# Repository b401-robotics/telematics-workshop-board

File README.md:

<!-- center -->
<h1 align="center">Telematics Workshop Board</h1>

<p align="center">
	</a>
	</a>
	</a>
</p>

This repository contains the documentation for the Workshop Telematics Board. The board is based on the ESP8266 microcontroller and has several features that can be used for various projects.

<!-- beritahu versi lawas -->
> For the previous version of the board, refer to the [v1 board.](https://github.com/b401-robotics/esp8266-minsys)

## 🌟 Features

The following are the features available on this board.

- ESP-12F (ESP8266)
- 8 GPIO Pins
- Programmable RGB LED
- Overcurrent Protection
- USB Type-C Connector (_Power Delivery Support_) 

## 👀 Preview

Here is a preview of the board that will be used in the workshop.

## 📚 Resources

For more information about the board, you can check the following resources.

- [Hardware](hardware/)
- [Firmware](firmware/)

## 🔮 Project Showcase

Discover projects that use this board in various applications and contexts.

- [🌌 __COMING SOON__]() by [farisrfp](https://farisrfp.me)

## 📝 License

Distributed under the MIT License. See `LICENSE` for more information.

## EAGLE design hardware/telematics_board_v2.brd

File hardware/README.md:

# **Hardware**

This folder contains the hardware design for the Telematics Workshop Board.

## 🚀 Getting Started

### Prerequisites

- [Eagle](https://www.autodesk.com/products/eagle/overview) 
- [Fusion 360](https://www.autodesk.com/products/fusion-360/overview)

## 🕸 Schematic

This is the schematic diagram for the Board will be used in the workshop.

## 💲 Bill of Material

|   Designator   | Quantity | Package | Value  |      Description      |
|:--------------:|:--------:|:-------:|:------:|:---------------------:|
|    ESP-12F     |    1     |    -    |   -    |    ESP8266 Module     |
|       U1       |    1     | SOP-16  | CH340C |    IC USB to UART     |
|       U2       |    1     | SOT-223 |  3V3   | Voltage Regulator 3V3 |
|       D1       |    1     |  0805   |  Red   |          LED          |
|      NEO       |    1     |  5050   |  RGB   |        WS2812B        |
|       F1       |    1     |  1206   | 750mA  |    Resettable Fuse    |
|       J1       |    1     |    -    |  16P   |      USB Type-C       |
|   BOOT, RST    |    2     |    -    |   -    |      Push Button      |
| R1, R2, R3, R4 |    4     |  0805   |  10K   |       Resistor        |
|     R5, R6     |    2     |  0805   |  5.1K  |       Resistor        |
|       R7       |    1     |  0805   |   1K   |       Resistor        |
|       C1       |    1     |  2412   |  100u  |   Capacitor (Polar)   |
|     C2, C3     |    2     |  0805   |  10u   | Capacitor (Nonpolar)  |
|       C4       |    1     |  0805   |   1u   | Capacitor (Nonpolar)  |
|       C5       |    1     |  0805   |  10n   | Capacitor (Nonpolar)  |
|     Q1, Q2     |    2     | SOT-23  | BSS138 |   N-Channel MOSFET    |

## 👨‍🔧 PCB Assembly

Refer to the image below for detailed placement and routing.

> Click the image to view the full resolution.

### SMD Polarity

SMD LEDs have 2 pins, namely the anode and cathode pins. Refer to the image below to determine which pin is the anode and cathode.

The Tantalum Capacitor is one of the polar capacitors. Refer to the image below to determine which pin is the anode(+).

## 📚 Resources

### Telematics Workshop Board

Access the design files for the Telematics Workshop Board directly from this repository:

- [Schematic](./telematics_board_v2.sch)
- [Board Design](./telematics_board_v2.brd)
- [3D Model](./telematics_board_v2.step)
- [Eagle/Fusion 360 Library](libraries/)

### Enclosure

Access the 3D printable enclosure files from this repository, with contributions from the following individuals:

- [B401 Robotics]()

<!-- ## SMD Polarity

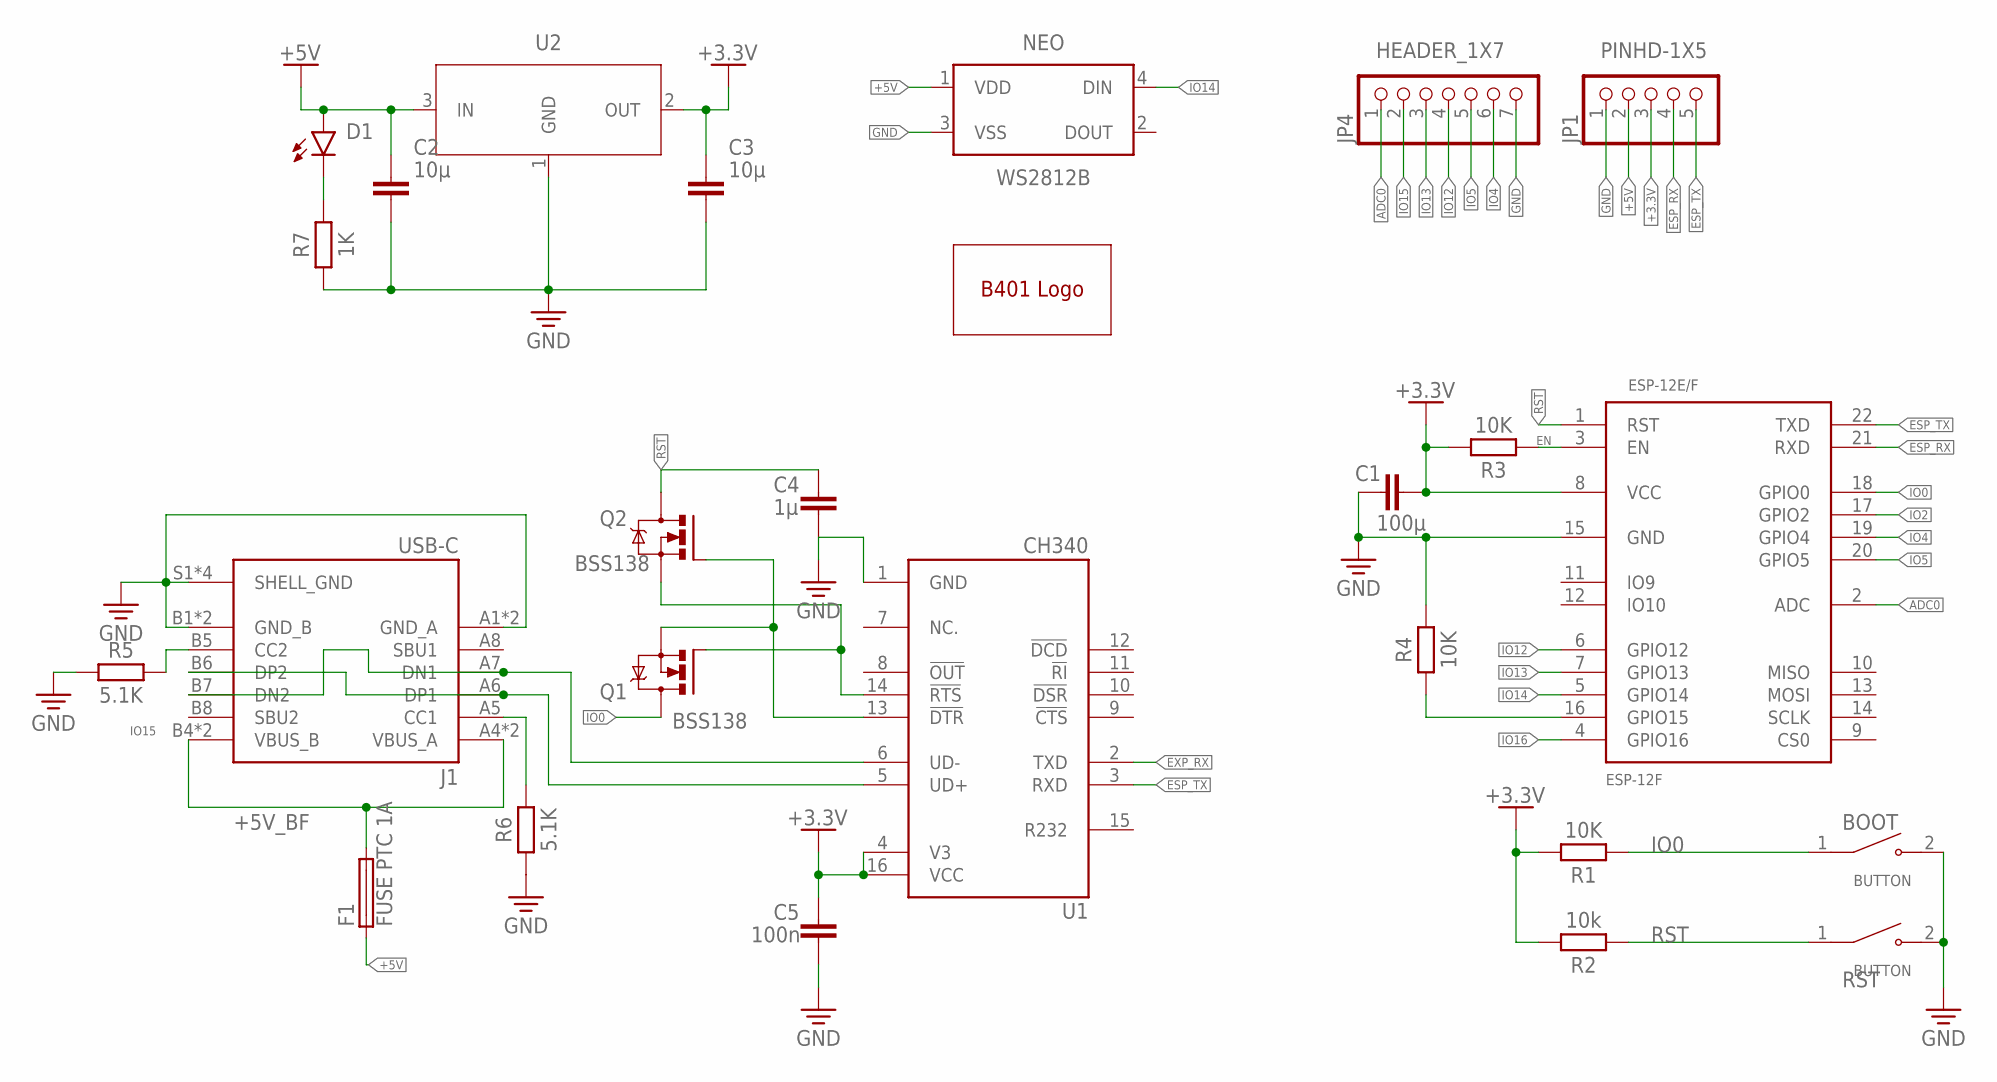
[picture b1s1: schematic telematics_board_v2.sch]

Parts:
BOOT: BUTTON; SWITCH-2P
C1: 100µ; CAPM6032X280
C2, C3: 10µ; CAPC2012X110
C4: 1µ; CAPC2012X110
C5: 100n; CAPC2012X110
D1: LED_RED; LEDC2012X110N_FLAT-R
ESP-12E/F: ESP-12F
F1: FUSE PTC 1A; FUSC3215X82N
J1: USB-C; USB-C-16P
JP1: PINHD-1X5; 1X05
JP4: HEADER_1X7; 1X07
NEO: WS2812B
Q1, Q2: BSS138; SOT23
R1, R3, R4: 10K; RESC2012X65
R2: 10k; RESC2012X65
R5, R6: 5.1K; RESC2012X65
R7: 1K; RESC2012X65
RST: BUTTON; SWITCH-2P
U1: CH340; SOIC127P600X180-16N
U2: NCP1117ST33T3G; SOT230P700X170-4
U$1: LOGO_B401LARGE; B401_LARGE

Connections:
+3.3V: C1.2, C3.1, C5.1, ESP-12E/F.8 (VCC), JP1.3, R1.2, R2.2, R3.2, U1.4 (V3), U1.16 (VCC), U2.2 (OUT)
+5V: C2.1, D1.A, F1.1, JP1.2, NEO.1 (VDD), U2.3 (IN)
+5V_BF: F1.2, J1.A4 (VBUS_A), J1.A9 (VBUS_A), J1.B4 (VBUS_B), J1.B9 (VBUS_B)
ADC0: ESP-12E/F.2 (ADC), JP4.1
EN: ESP-12E/F.3 (EN), R3.1
ESP_RX: ESP-12E/F.21 (RXD), JP1.4
ESP_TX: ESP-12E/F.22 (TXD), JP1.5, U1.3 (RXD)
EXP_RX: U1.2 (TXD)
GND: BOOT.2, C1.1, C2.2, C3.2, C4.2, C5.2, ESP-12E/F.15 (GND), J1.A1 (GND_A), J1.A12 (GND_A), J1.B1 (GND_B), J1.B12 (GND_B), J1.S1 (SHELL_GND), J1.S2 (SHELL_GND), J1.S3 (SHELL_GND), J1.S4 (SHELL_GND), JP1.1, JP4.7, NEO.3 (VSS), R4.2, R5.1, R6.1, R7.1, RST.2, U1.1 (GND), U2.1 (GND)
IO0: BOOT.1, ESP-12E/F.18 (GPIO0), Q1.3 (D), R1.1
IO2: ESP-12E/F.17 (GPIO2)
IO4: ESP-12E/F.19 (GPIO4), JP4.6
IO5: ESP-12E/F.20 (GPIO5), JP4.5
IO12: ESP-12E/F.6 (GPIO12), JP4.4
IO13: ESP-12E/F.7 (GPIO13), JP4.3
IO14: ESP-12E/F.5 (GPIO14), NEO.4 (DIN)
IO15: ESP-12E/F.16 (GPIO15), JP4.2, R4.1
IO16: ESP-12E/F.4 (GPIO16)
unnamed: J1.A6 (DP1), J1.B6 (DP2), U1.5 (UD+)
unnamed: J1.A7 (DN1), J1.B7 (DN2), U1.6 (UD-)
unnamed: Q1.2 (S), Q2.1 (G), U1.13 (!DTR)
unnamed: J1.B5 (CC2), R5.2
unnamed: J1.A5 (CC1), R6.2
unnamed: Q1.1 (G), Q2.2 (S), U1.14 (!RTS)
unnamed: D1.C, R7.2
RST: C4.1, ESP-12E/F.1 (RST), Q2.3 (D), R2.1, RST.1

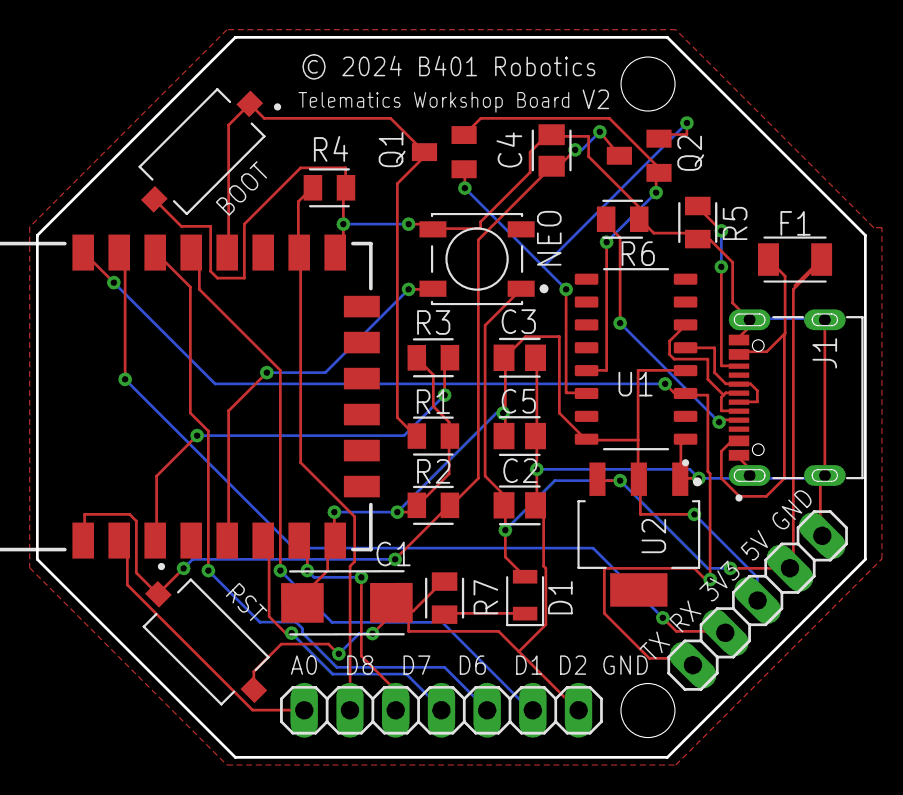
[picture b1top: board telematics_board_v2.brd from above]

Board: 2 copper layers, 46.0 x 40.0 mm, 26 parts (1 on the bottom side), 23 nets.

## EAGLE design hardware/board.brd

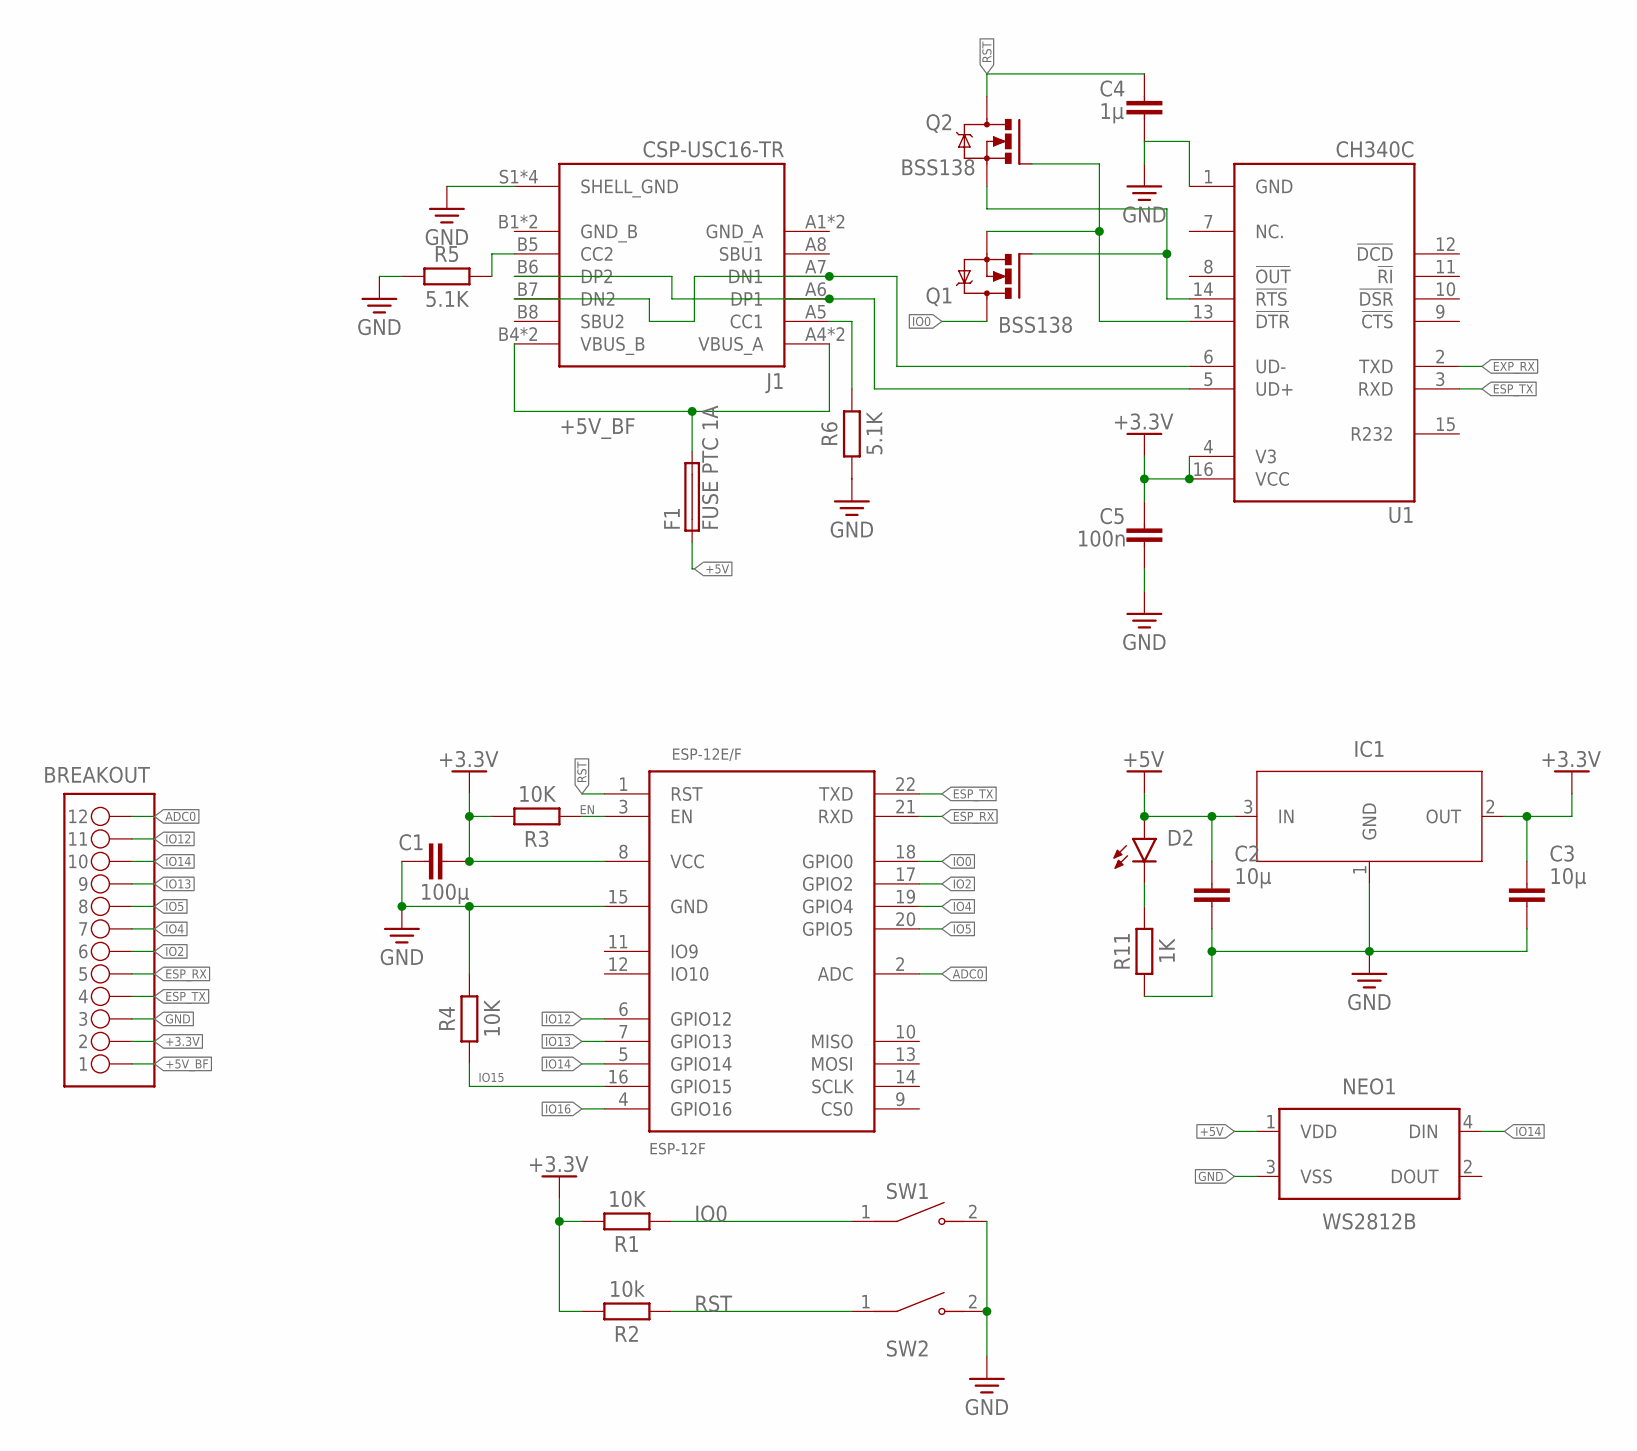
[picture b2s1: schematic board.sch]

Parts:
BREAKOUT: PINHD-1X12-BACKUP_1X12M; 1X12
C1: 100µ; CAPM6032X280
C2, C3: 10µ; CAPC2012X110
C4: 1µ; CAPC2012X110
C5: 100n; CAPC2012X110
D2: LED_RED; LEDC2012X110N_FLAT-R
ESP-12E/F: ESP-12F
F1: FUSE PTC 1A; FUSC3215X82N
IC1: NCP1117ST33T3G; SOT230P700X170-4
J1: CSP-USC16-TR; VALCON_CSP-USC16-TR
NEO1: WS2812B
Q1, Q2: BSS138; SOT23
R1, R3, R4: 10K; RESC2012X65
R2: 10k; RESC2012X65
R5, R6: 5.1K; RESC2012X65
R11: 1K; RESC2012X65
SW1, SW2: SWITCH-2P
U1: CH340C; SOIC127P600X180-16N

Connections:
+3.3V: BREAKOUT.2, C1.2, C3.1, C5.1, ESP-12E/F.8 (VCC), IC1.2 (OUT), R1.2, R2.2, R3.2, U1.4 (V3), U1.16 (VCC)
+5V: C2.1, D2.A, F1.1, IC1.3 (IN), NEO1.1 (VDD)
+5V_BF: BREAKOUT.1, F1.2, J1.A4 (VBUS_A), J1.A9 (VBUS_A), J1.B4 (VBUS_B), J1.B9 (VBUS_B)
ADC0: BREAKOUT.12, ESP-12E/F.2 (ADC)
EN: ESP-12E/F.3 (EN), R3.1
ESP_RX: BREAKOUT.5, ESP-12E/F.21 (RXD)
ESP_TX: BREAKOUT.4, ESP-12E/F.22 (TXD), U1.3 (RXD)
EXP_RX: U1.2 (TXD)
GND: BREAKOUT.3, C1.1, C2.2, C3.2, C4.2, C5.2, ESP-12E/F.15 (GND), IC1.1 (GND), J1.S1 (SHELL_GND), J1.S2 (SHELL_GND), J1.S3 (SHELL_GND), J1.S4 (SHELL_GND), NEO1.3 (VSS), R4.2, R5.1, R6.1, R11.1, SW1.2, SW2.2, U1.1 (GND)
GND_A: J1.A1 (GND_A), J1.A12 (GND_A)
GND_B: J1.B1 (GND_B), J1.B12 (GND_B)
IO0: ESP-12E/F.18 (GPIO0), Q1.3 (D), R1.1, SW1.1
IO2: BREAKOUT.6, ESP-12E/F.17 (GPIO2)
IO4: BREAKOUT.7, ESP-12E/F.19 (GPIO4)
IO5: BREAKOUT.8, ESP-12E/F.20 (GPIO5)
IO12: BREAKOUT.11, ESP-12E/F.6 (GPIO12)
IO13: BREAKOUT.9, ESP-12E/F.7 (GPIO13)
IO14: BREAKOUT.10, ESP-12E/F.5 (GPIO14), NEO1.4 (DIN)
IO15: ESP-12E/F.16 (GPIO15), R4.1
IO16: ESP-12E/F.4 (GPIO16)
unnamed: J1.A6 (DP1), J1.B6 (DP2), U1.5 (UD+)
unnamed: J1.A7 (DN1), J1.B7 (DN2), U1.6 (UD-)
unnamed: Q1.2 (S), Q2.1 (G), U1.13 (!DTR)
unnamed: J1.B5 (CC2), R5.2
unnamed: J1.A5 (CC1), R6.2
unnamed: Q1.1 (G), Q2.2 (S), U1.14 (!RTS)
unnamed: D2.C, R11.2
RST: C4.1, ESP-12E/F.1 (RST), Q2.3 (D), R2.1, SW2.1

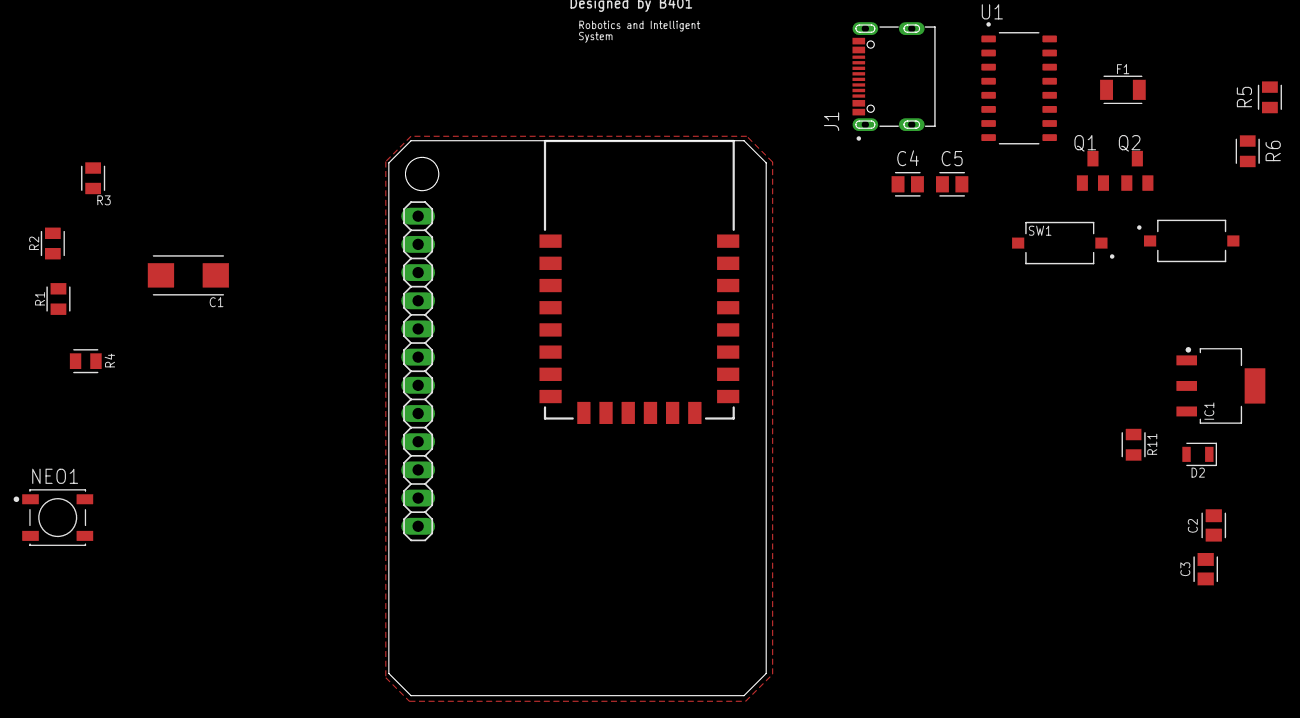
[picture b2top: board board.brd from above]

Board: 2 copper layers, 24 parts (0 on the bottom side), 26 nets.

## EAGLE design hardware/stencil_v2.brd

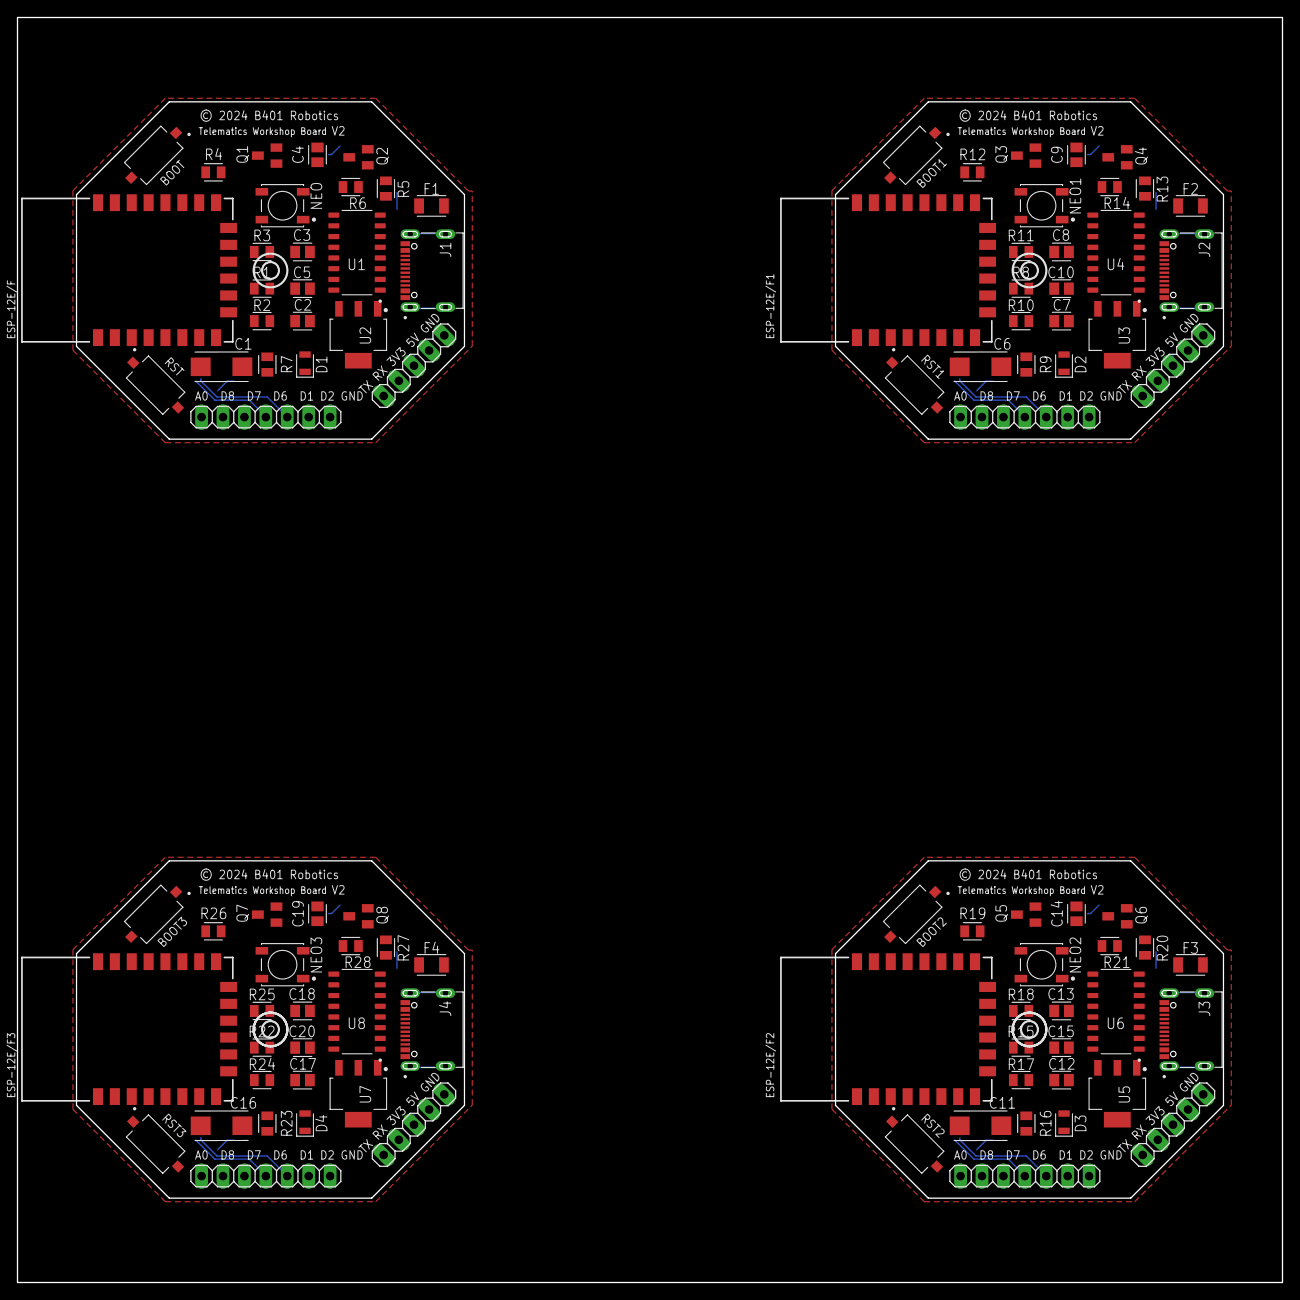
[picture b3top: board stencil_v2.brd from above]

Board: 2 copper layers, 150.0 x 150.0 mm, 100 parts (0 on the bottom side), 88 nets.

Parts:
BOOT, BOOT1, BOOT2, BOOT3: BUTTON; SWITCH-2P
C1, C6, C11, C16: 100µ; CAPM6032X280
C2, C3, C7, C8, C12, C13, C17, C18: 10µ; CAPC2012X110
C4, C9, C14, C19: 1µ; CAPC2012X110
C5, C10, C15, C20: 100n; CAPC2012X110
D1, D2, D3, D4: LED_RED; LEDC2012X110N_FLAT-R
ESP-12E/F, ESP-12E/F1, ESP-12E/F2, ESP-12E/F3: ESP-12F
F1, F2, F3, F4: FUSE PTC 1A; FUSC3215X82N
J1, J2, J3, J4: USB-C; USB-C-16P
JP1, JP3, JP6, JP8: PINHD-1X5; 1X05
JP2, JP4, JP5, JP7: HEADER_1X7; 1X07
NEO, NEO1, NEO2, NEO3: WS2812B
Q1, Q2, Q3, Q4, Q5, Q6, Q7, Q8: BSS138; SOT23
R1, R3, R4, R8, R11, R12, R15, R18, R19, R22, R25, R26: 10K; RESC2012X65
R2, R10, R17, R24: 10k; RESC2012X65
R5, R6, R13, R14, R20, R21, R27, R28: 5.1K; RESC2012X65
R7, R9, R16, R23: 1K; RESC2012X65
RST, RST1, RST2, RST3: BUTTON; SWITCH-2P
U1, U4, U6, U8: CH340; SOIC127P600X180-16N
U2, U3, U5, U7: NCP1117ST33T3G; SOT230P700X170-4

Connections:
+3.3V: C3.1, C5.1, U1.4, U1.16, U2.2
+3.3V1: C8.1, C10.1, U3.2, U4.4, U4.16
+3.3V2: C13.1, C15.1, U5.2, U6.4, U6.16
+3.3V3: C18.1, C20.1, U7.2, U8.4, U8.16
+5V: F1.1, JP1.2
+5V1: F2.1, JP3.2
+5V2: F3.1, JP6.2
+5V3: F4.1, JP8.2
+5V_BF: F1.2, J1.A4, J1.A9, J1.B4, J1.B9
+5V_BF1: F2.2, J2.A4, J2.A9, J2.B4, J2.B9
+5V_BF2: F3.2, J3.A4, J3.A9, J3.B4, J3.B9
+5V_BF3: F4.2, J4.A4, J4.A9, J4.B4, J4.B9
ADC0: ESP-12E/F.2, JP4.1
ADC1: ESP-12E/F1.2, JP2.1
ADC2: ESP-12E/F2.2, JP5.1
ADC3: ESP-12E/F3.2, JP7.1
ESP_TX: JP1.5, U1.3
ESP_TX1: JP3.5, U4.3
ESP_TX2: JP6.5, U6.3
ESP_TX3: JP8.5, U8.3
GND: C4.2, J1.A1, J1.A12, J1.B1, J1.B12, J1.S1, J1.S2, J1.S3, J1.S4, JP1.1, NEO.3, R5.1, R6.1
GND1: C9.2, J2.A1, J2.A12, J2.B1, J2.B12, J2.S1, J2.S2, J2.S3, J2.S4, JP3.1, NEO1.3, R13.1, R14.1
GND2: C14.2, J3.A1, J3.A12, J3.B1, J3.B12, J3.S1, J3.S2, J3.S3, J3.S4, JP6.1, NEO2.3, R20.1, R21.1
GND3: C19.2, J4.A1, J4.A12, J4.B1, J4.B12, J4.S1, J4.S2, J4.S3, J4.S4, JP8.1, NEO3.3, R27.1, R28.1
IO0: BOOT.1, ESP-12E/F.18, Q1.3, R1.1
IO1: BOOT1.1, ESP-12E/F1.18, Q3.3, R8.1
IO3: ESP-12E/F1.6, JP2.4
IO12: ESP-12E/F.6, JP4.4
IO15: ESP-12E/F.16, JP4.2, R4.1
IO17: ESP-12E/F1.16, JP2.2, R12.1
IO18: BOOT2.1, ESP-12E/F2.18, Q5.3, R15.1
IO19: ESP-12E/F2.6, JP5.4
IO26: ESP-12E/F2.16, JP5.2, R19.1
IO27: BOOT3.1, ESP-12E/F3.18, Q7.3, R22.1
IO28: ESP-12E/F3.6, JP7.4
IO35: ESP-12E/F3.16, JP7.2, R26.1
unnamed: J1.A6, J1.B6, U1.5
unnamed: J1.A7, J1.B7, U1.6
unnamed: Q1.2, Q2.1
unnamed: J1.B5, R5.2
unnamed: D1.C, R7.2
unnamed: D2.C, R9.2
unnamed: J2.A6, J2.B6, U4.5
unnamed: J2.A7, J2.B7, U4.6
unnamed: Q3.2, Q4.1
unnamed: J2.B5, R13.2
unnamed: D3.C, R16.2
unnamed: J3.A6, J3.B6, U6.5
unnamed: J3.A7, J3.B7, U6.6
unnamed: Q5.2, Q6.1
unnamed: J3.B5, R20.2
unnamed: D4.C, R23.2
unnamed: J4.A6, J4.B6, U8.5
unnamed: J4.A7, J4.B7, U8.6
unnamed: Q7.2, Q8.1
unnamed: J4.B5, R27.2
RST: C4.1, Q2.3, R2.1
RST1: C9.1, Q4.3, R10.1
RST2: C14.1, Q6.3, R17.1
RST3: C19.1, Q8.3, R24.1
S$1: C1.2, ESP-12E/F.8
S$2: R1.2, R2.2, R3.2
S$4: C1.1, C2.2, C3.2, C5.2, JP4.7, R7.1, RST.2
S$5: U1.1, U2.1
S$6: BOOT.2, ESP-12E/F.15, R4.2
S$7: ESP-12E/F.1, RST.1
S$11: C2.1, D1.A, NEO.1
S$21: C6.2, ESP-12E/F1.8
S$22: R8.2, R10.2, R11.2
S$24: U3.1, U4.1
S$25: C6.1, C7.2, C8.2, C10.2, JP2.7, R9.1, RST1.2
S$26: BOOT1.2, ESP-12E/F1.15, R12.2
S$27: ESP-12E/F1.1, RST1.1
S$32: C7.1, D2.A, NEO1.1
S$41: C11.2, ESP-12E/F2.8
S$42: R15.2, R17.2, R18.2
S$44: U5.1, U6.1
S$45: C11.1, C12.2, C13.2, C15.2, JP5.7, R16.1, RST2.2
S$46: BOOT2.2, ESP-12E/F2.15, R19.2
S$47: ESP-12E/F2.1, RST2.1
S$52: C12.1, D3.A, NEO2.1
S$61: C16.2, ESP-12E/F3.8
S$62: R22.2, R24.2, R25.2
S$64: U7.1, U8.1
S$65: C16.1, C17.2, C18.2, C20.2, JP7.7, R23.1, RST3.2
S$66: BOOT3.2, ESP-12E/F3.15, R26.2
S$67: ESP-12E/F3.1, RST3.1
S$72: C17.1, D4.A, NEO3.1

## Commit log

2024-05-13 chore: Update board name and fix typos in README files
2024-05-13 doc: add missing file
2024-05-14 fix readme di hardware ada yg salah
2024-05-27 chore: Update board name, fix typos, and add missing file in README files
2024-06-07 Update LED pin and serial baud rate, and generate random color with reduced intensity
2024-06-07 fix baudrate di platform.ini & tambah fungsi utk mematikan rgb led

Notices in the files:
hardware/stencil_v2.brd:
© 2024 B401 Robotics
